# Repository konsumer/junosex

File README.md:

# Control Roland Alpha Juno 1, 2, 106 & MKS-50 with MIDI CC, instead of SysEx

All decent MIDI sequencers speak CC, but being able to speak SysEx particular to these synths is harder to come by.  This code, when placed on an ATMEGA8/168/328 will do the conversion for you, and allow your computer/ipad/sequencer to get romantic with your Juno.

There are 2 versions. One is a software implementation, and one is an Arduino-based version. I made several options for putting it together in either form.

## Software Version

I  made a CLI-version, and a GUI version.

### command-line

To install the CLI dependencies, run this, in the software directory:

    npm install

You can get help with:

    ./junosex --help

### GUI

I only tested this on Mac, so that is the only platform I included, but the process should be fairly similar. For Mac, just extract software/JunoSex-mac.zip, and run. For other platforms, you can run `npm install` to build MIDI, put the contents of junosex.nw (make package.json be in root) into a zip file and change the extension to `.nw`, which should make it run if you have the [node-webkit] runtime installed. They also have some info on building a stand-alone app on their site.

The build process is the same as CLI, using the software/junosex.nw directory and the [node-webkit] runtime for your system. I had to use `nw-gyp` to make it build the MIDI library for 32bit (a current limitation of [node-webkit]: Mac requires 32bit versions of everything.) but Mac-peeps should be covered with premade zipfile.

## Hardware Version

The hardware version can be made with an Arduino and a [MIDI shield] or [MIDI breakout], or you can make it on a custom PCB with an ATMEGA chip, or a [cheap-o USB-to-MIDI adapter] and an ATMEGA/Arduino.

The [Arduino MIDI Library] is required. I compiled the code in the Arduino IDE.

### Arduino

The arduino/shield route just requires that you put them together, and run the Arduino code (junosex.ino.) This should take about 5 minutes to complete.

### Custom PCB / ATMEGA

Follow the [schematic] to put it together. I will provide better instructions, later. I used [ArduinoISP] running on a [teensy] to program an [ATMEGA8]. I used a [resonator] to be cheap and lazy (rather than a crystal and 2 capacitors.)

If you want it to run on batteries, use a 9V battery and a [7805 regulator].

I made a full [parts list], for mouser, to build what is listed in the schematic. I just picked parts that are cheap and available. Feel free to choose replacements.

### [cheap-o USB-to-MIDI adapter]

If you are using a [cheap-o USB-to-MIDI adapter], you can open it up, and solder the wires direct to TX/RX, and use the power/ground from USB (inside adapter) to make it all simpler/cheaper.

### Modification

Feel free to modify. This thing is super-simple.

Some ideas:
* put RGB LEDs on PWM pins, for cool light-effects when different control messages are sent
* add knobs to change how CCs are interpreted, or set values directly
* Attach [wireless] to it for cheap, so you can hide your computer/sequencer.

[ATMEGA8]: http://www.mouser.com/ProductDetail/Atmel/ATMEGA8-16PU/?qs=7JStj%2fjQ2SHlSx6QootzDTUTMpkFcVaHHuOB6ZSDMnk%3d
[resonator]: http://www.mouser.com/Search/ProductDetail.aspx?R=HWZT-16.00MDvirtualkey52750000virtualkey815-HWZT-16.00MD
[ArduinoISP]: http://arduino.cc/en/Tutorial/ArduinoISP
[Arduino MIDI Library]: http://arduino.cc/playground/Main/MIDILibrary
[wireless]: http://www.sparkfun.com/products/10532
[teensy]: http://www.pjrc.com/store/teensy.html
[cheap-o USB-to-MIDI adapter]: http://shiftmore.blogspot.com/2010/01/quick-and-dirty-arduino-midi-over-usb.html
[schematic]: https://github.com/konsumer/junosex/raw/master/schematic.png
[7805 regulator]: http://www.mouser.com/ProductDetail/ON-Semiconductor/MC7805CTG/?qs=%252b9%2fcbd0IE0RkDYggsVZtGe3PoqBzrkPO
[parts list]: http://www.mouser.com/ProjectManager/ProjectDetail.aspx?AccessID=fe0a4b4498
[MIDI shield]: https://www.sparkfun.com/products/9595
[MIDI breakout]: https://www.sparkfun.com/products/9598
[node-webkit]: https://github.com/rogerwang/node-webkit

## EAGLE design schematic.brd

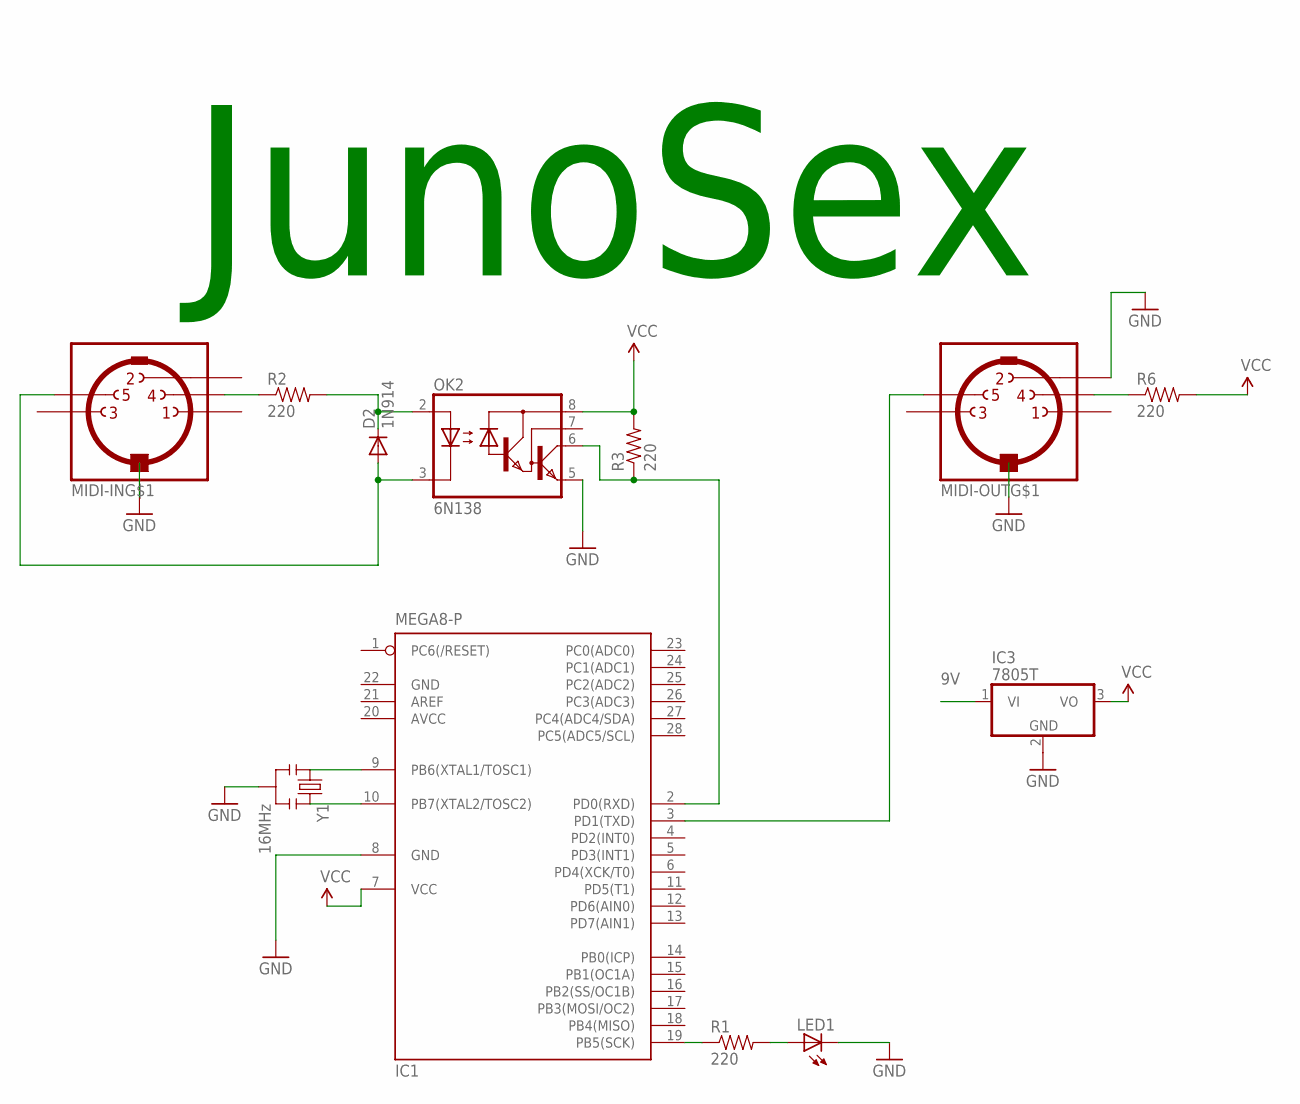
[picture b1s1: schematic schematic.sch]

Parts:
D2: 1N914; DIODE-1N4148
IC1: MEGA8-P; DIL28-3
IC3: 7805T; TO220H
LED1: LED5MM
MIDI-IN: MIDIJACK; CP-2350
MIDI-OUT: MIDIJACK; CP-2350
OK2: 6N138; DIL08
R1, R2, R3, R6: 220; AXIAL-0.3
Y1: 16MHz; RESONATOR-PTH

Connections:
9V: IC3.1 (VI)
AVCC: IC1.20 (AVCC)
GND: IC1.8 (GND), IC1.22 (GND), IC3.2 (GND), LED1.K (C), MIDI-OUT.2, OK2.5 (GND), Y1.2
unnamed: IC1.9 (PB6(XTAL1/TOSC1)), Y1.1
unnamed: IC1.10 (PB7(XTAL2/TOSC2)), Y1.3
unnamed: MIDI-IN.4, R2.P$1 (1)
unnamed: D2.A, MIDI-IN.5, OK2.3 (C)
unnamed: D2.C, OK2.2 (A), R2.P$2 (2)
unnamed: MIDI-OUT.4, R6.P$1 (1)
unnamed: IC1.2 (PD0(RXD)), OK2.6 (VO), R3.P$1 (1)
unnamed: IC1.3 (PD1(TXD)), MIDI-OUT.5
unnamed: IC1.19 (PB5(SCK)), R1.P$1 (1)
unnamed: LED1.A, R1.P$2 (2)
VCC: IC1.7 (VCC), IC3.3 (VO), OK2.8 (VCC), R3.P$2 (2), R6.P$2 (2)

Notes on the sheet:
JunoSex

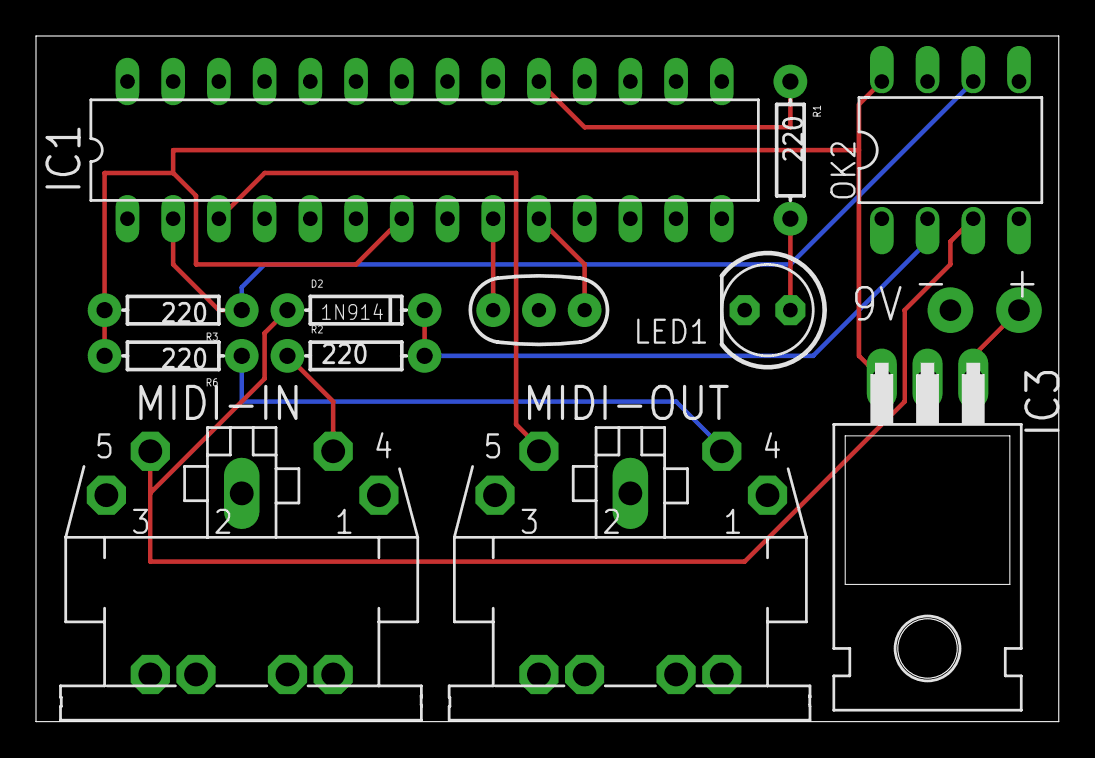
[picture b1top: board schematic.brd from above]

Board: 2 copper layers, 56.8 x 38.1 mm, 12 parts (0 on the bottom side), 12 nets.

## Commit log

2012-06-11 updated code comments to better reflect hardware.
2012-06-11 fixed symlinks
2012-06-11 updated comment, better, for hardware.
2012-06-11 Made comments clearer
2012-06-11 added label to schematic
2012-06-11 updated label of photo coupler to match mine
2012-06-11 updated schematic source, also
2012-06-13 faster control_map lookup in arduino code, using better optocoupler in schematic
2012-06-13 better array init, test for 0xFF instead of 0, so first param works
2012-06-13 Slightly more hardware info.
2012-06-13 forgot the "a"
2012-06-13 Better storage of control_map
2012-06-13 explained cheap-o hardware option
2012-06-13 I love 1-char commits
2012-06-13 added link to schematic image
2012-06-13 info about running on betteries
2012-06-13 info about compiler
2012-06-13 Created gh-pages branch via GitHub
2012-06-26 better schematic support
2012-06-27 added mouser parts list
2012-12-17 added software version
2012-12-18 moving things around
2012-12-18 improved docs
2012-12-18 perms for CLI
2012-12-18 docs for CLI
2013-01-02 Better cheap-o link, explains how to do it.

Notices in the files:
parts and their libraries:
SparkFun: Licensing: CC v3.0 Share-Alike You are welcome to use this library for commercial purposes.
